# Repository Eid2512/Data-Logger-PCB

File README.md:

# ATmega328P Data Logger PCB

A custom **two-layer embedded data-logger PCB** designed in KiCad around the **ATmega328P** microcontroller.

The board integrates external non-volatile memory, a real-time clock, user/status interfaces, and communication headers to provide a flexible hardware platform for data acquisition and logging applications.

## Project Overview

The board was designed to combine the core hardware required for an embedded data-logging system on a single PCB.

Key functions include:

* ATmega328P microcontroller
* External EEPROM for non-volatile data storage
* Real-Time Clock for timestamping
* I2C, SPI, and UART communication interfaces
* MCU GPIO expansion headers
* Status LEDs and user input
* External power connection
* Manufacturing Gerber and drill outputs

## Hardware Architecture

```text
                   ┌─────────────────┐
                   │    ATmega328P   │
                   └───────┬─────────┘
                           │
          ┌────────────────┼────────────────┐
          │                │                │
          ▼                ▼                ▼
     External EEPROM    DS1337 RTC      I/O Expansion
          │                │         ┌──────┼──────┐
          │                │         │      │      │
         I2C              I2C       UART   SPI    GPIO
```

## Main Components

### ATmega328P

The ATmega328P acts as the main controller of the data-logger board and provides the processing and peripheral interfaces required by the system.

### External EEPROM

The design includes **two 24LC1025 EEPROM devices** to provide additional non-volatile storage for logged data.

The EEPROM devices communicate with the MCU through the I2C interface.

### DS1337 Real-Time Clock

A **DS1337S I2C Real-Time Clock** provides date/time information that can be used to timestamp logged data.

### Communication Interfaces

Dedicated headers expose the MCU communication peripherals:

* **I2C**
* **SPI**
* **UART**

Additional headers expose MCU GPIO from Ports B, C, and D for sensor or peripheral expansion.

## PCB Design

**EDA Tool:** KiCad
**PCB Layers:** 2
**Board Material:** FR-4
**Board Thickness:** 1.6 mm

The design includes:

* Front and back copper routing
* Ground and power distribution
* Through-hole interface connectors
* SMD components
* Silkscreen component identification
* Mounting holes
* Gerber and drill manufacturing outputs

## PCB Layout

## 3D View

## Expansion Interfaces

The board exposes dedicated connectors for:

| Interface | Purpose                              |
| --------- | ------------------------------------ |
| I2C       | Sensors and external I2C peripherals |
| SPI       | SPI-based sensors/peripherals        |
| UART      | Serial communication and debugging   |
| PORTB     | MCU GPIO expansion                   |
| PORTC     | MCU GPIO expansion                   |
| PORTD     | MCU GPIO expansion                   |

## Repository Structure

```text
ATmega328P-Data-Logger-PCB/
├── hardware/
│   ├── data-logger.kicad_pro
│   ├── data-logger.kicad_sch
│   ├── connectors.kicad_sch
│   └── data-logger.kicad_pcb
├── manufacturing/
│   ├── gerber/
│   └── drill/
├── images/
│   ├── layoyt.png
│   ├── pcb_3d_front.png
│   └── pcb-3d-back.png
├── docs/
│   └── data-logger-project.pdf
└── README.md
```

## Design Outputs

The repository includes the KiCad source files together with Gerber and drill outputs required for PCB fabrication.

## Skills Demonstrated

* Embedded hardware design
* Schematic capture
* PCB layout and routing
* ATmega328P system design
* I2C peripheral integration
* External EEPROM integration
* RTC integration
* UART/SPI/I2C interface breakout
* KiCad
* PCB manufacturing-file generation

## Project Scope

This repository focuses on the **hardware and PCB design** of the data-logger platform.

The project was completed through:

- Schematic capture
- PCB layout and routing
- Gerber generation
- Drill-file generation

The board was **not fabricated or physically validated**.

Firmware for complete data-logging functionality is outside the scope of this repository.

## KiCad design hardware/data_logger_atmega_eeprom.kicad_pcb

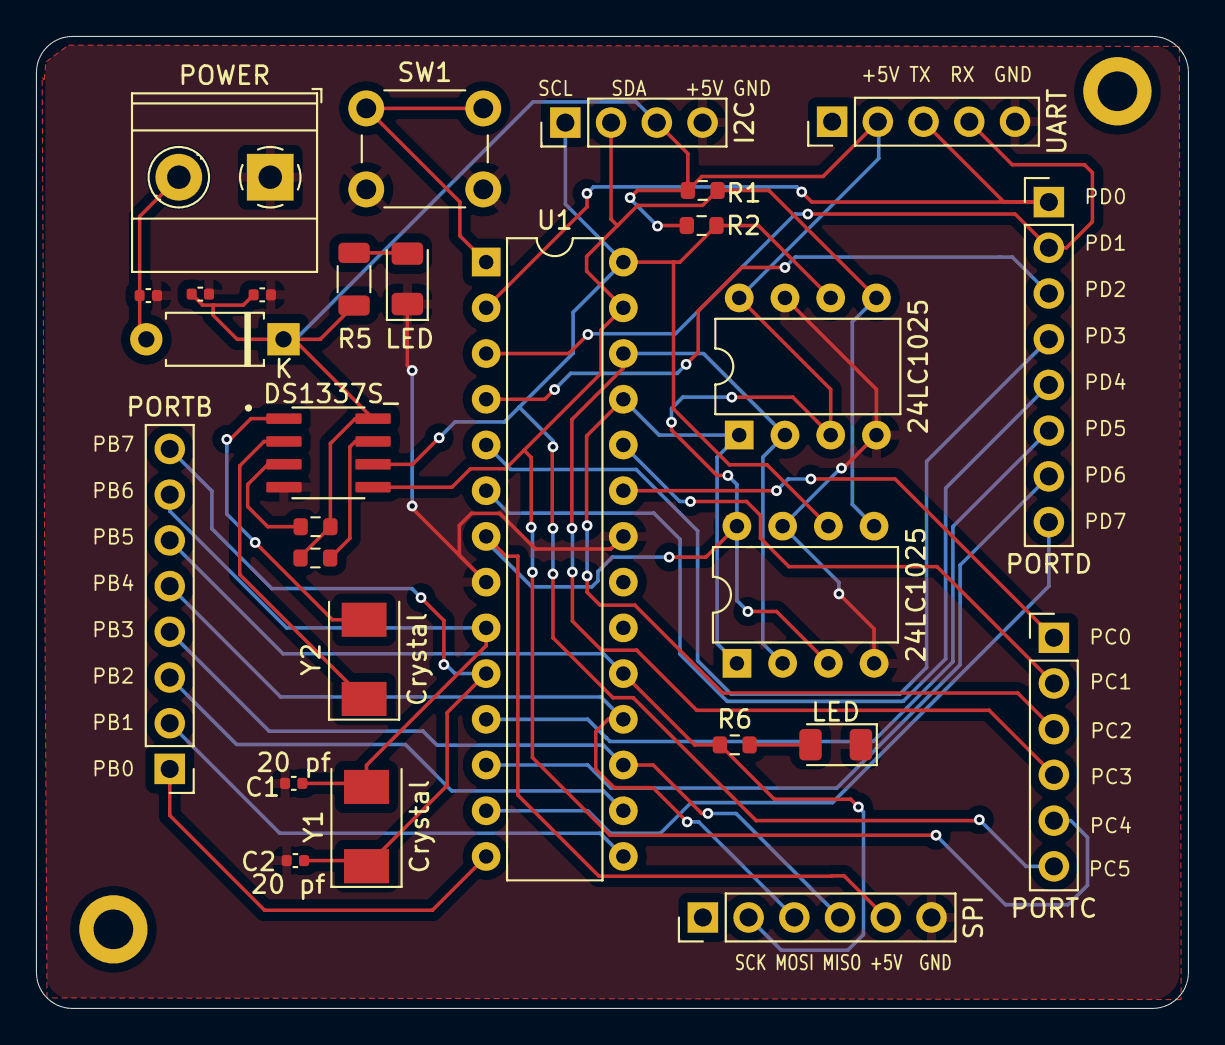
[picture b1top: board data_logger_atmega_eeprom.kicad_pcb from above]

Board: 2 copper layers, 64.0 x 54.0 mm, 30 parts (0 on the bottom side), 32 nets.

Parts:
C1, C2: 20 pf; C_0402_1005Metric
C3: 10uf; C_0402_1005Metric
C4, C5: 100nf; C_0402_1005Metric
D1: DIODE; D_A-405_P7.62mm_Horizontal
D2, D3: LED; LED_1206_3216Metric
H1, H2: MountingHole; MountingHole_2.2mm_M2_ISO14580_Pad
J1: I2C; PinHeader_1x04_P2.54mm_Vertical
J2: UART; PinHeader_1x05_P2.54mm_Vertical
J3: SPI; PinHeader_1x06_P2.54mm_Vertical
J4: PORTC; PinHeader_1x06_P2.54mm_Vertical
J5: PORTB; PinHeader_1x08_P2.54mm_Vertical
J6: PORTD; PinHeader_1x08_P2.54mm_Vertical
J7: POWER; TerminalBlock_Phoenix_MKDS-1,5-2-5.08_1x02_P5.08mm_Horizont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
R1, R2, R3, R4: R; R_0603_1608Metric
R5: R_Small; R_1206_3216Metric
R6: 330; R_0603_1608Metric
SW1: SW_Push; SW_PUSH_6mm_H4.3mm
U1: ATmega328-P; DIP-28_W7.62mm
U2, U3: 24LC1025; DIP-8_W7.62mm
U4: DS1337S_; SOIC127P600X175-8N
Y1, Y2: Crystal; Crystal_SMD_0603-2Pin_6.0x3.5mm

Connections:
+5V: C4.1, C5.1, D1.1 (K), J1.3, J2.2, J3.5, R1.2, R2.2, R3.1, R4.1, R5.1, U1.7 (VCC), U2.3 (A2), U2.8 (VCC), U3.3 (A2), U3.8 (VCC), U4.8 (VCC)
EEPROM1/PC2: J4.3, U1.25 (PC2), U2.1 (A0), U3.1 (A0)
EEPROM2/PC3: J4.4, U1.26 (PC3), U2.2 (A1), U3.2 (A1)
GND: C1.2, C2.2, C3.2, C4.2, C5.2, D2.1 (K), D3.1 (K), J1.4, J2.5, J3.6, J7.1, SW1.2, U1.8 (GND), U1.22 (GND), U2.4 (GND), U2.7 (WP), U3.4 (GND), U3.7 (WP), U4.4 (GND)
MISO/PB3: J3.4, J5.4, U1.17 (PB3)
MOSI/PB4: J3.3, J5.5, U1.18 (PB4)
unnamed: C3.1, D1.2 (A), J7.2
unnamed: D2.2 (A), R5.2
unnamed: D3.2 (A), R6.2
unnamed: SW1.1, U1.1 (~RESET/PC6)
unnamed: R3.2, U4.7 (SQW/~INT)
unnamed: U4.1 (X1), Y2.2
unnamed: U4.2 (X2), Y2.1
unnamed: R4.2, U4.3 (~INTA)
PB0: J5.1, U1.14 (PB0)
PB1: J5.2, U1.15 (PB1)
PB2: J5.3, U1.16 (PB2)
PC0: J4.1, U1.23 (PC0)
PC1: J4.2, U1.24 (PC1)
PD2: J6.3, U1.4 (PD2)
PD3: J6.4, U1.5 (PD3)
PD4: J6.5, U1.6 (PD4)
PD5: J6.6, U1.11 (PD5)
PD6: J6.7, U1.12 (PD6)
PD7: J6.8, U1.13 (PD7)
RX/PD1: J2.4, J6.2, U1.3 (PD1)
SCK/PB5: J3.2, J5.6, R6.1, U1.19 (PB5)
SCL/PC5: J1.1, J4.6, R2.1, U1.28 (PC5), U2.6 (SCL), U3.6 (SCL), U4.6 (SCL)
SDA/PC4: J1.2, J4.5, R1.1, U1.27 (PC4), U2.5 (SDA), U3.5 (SDA), U4.5 (SDA)
TX/PD0: J2.3, J6.1, U1.2 (PD0)
XTAL1/PB6: C1.1, J5.7, U1.9 (XTAL1/PB6), Y1.2
XTAL2/PB7: C2.1, J5.8, U1.10 (XTAL2/PB7), Y1.1
